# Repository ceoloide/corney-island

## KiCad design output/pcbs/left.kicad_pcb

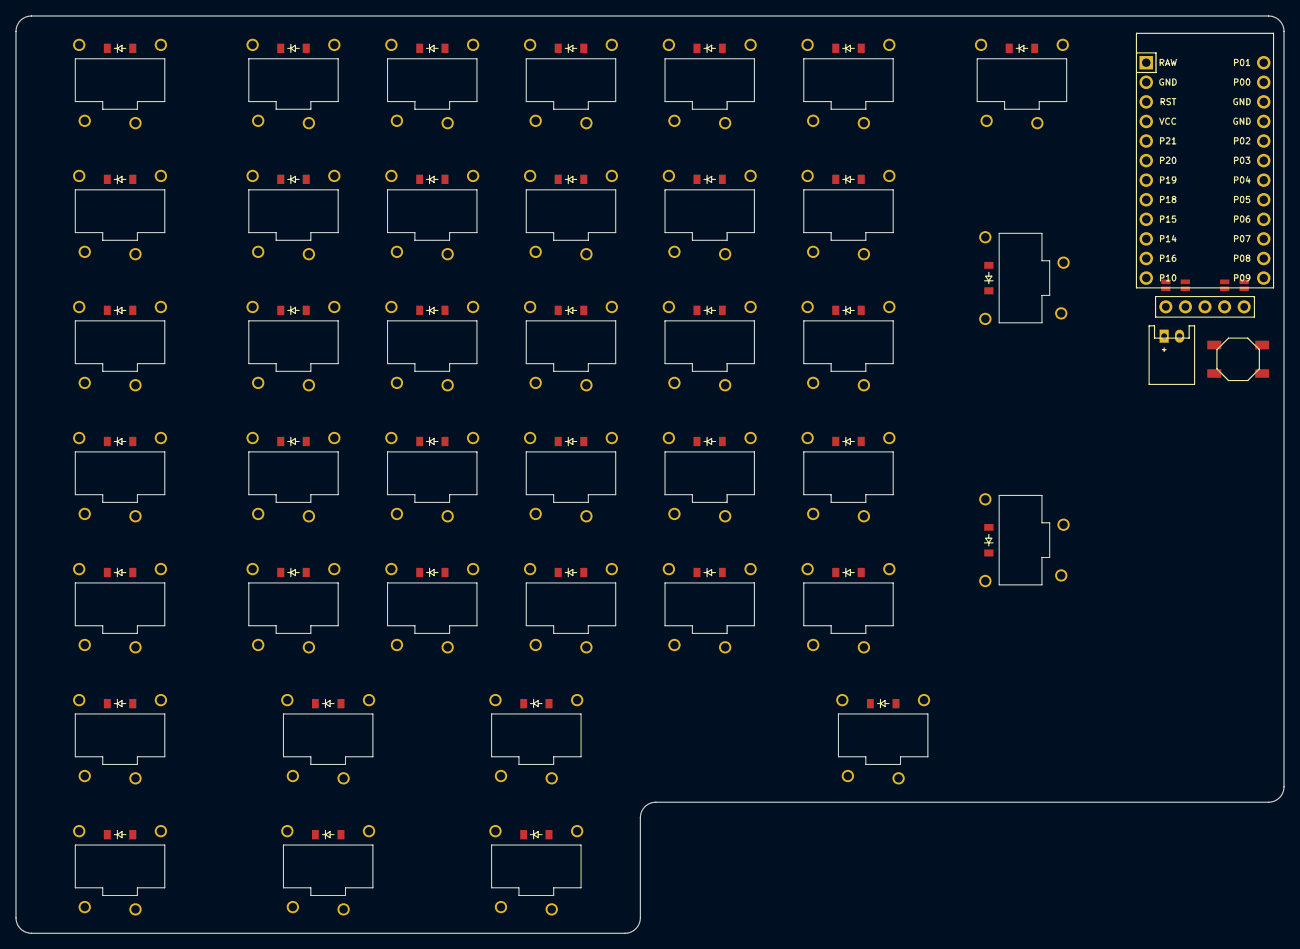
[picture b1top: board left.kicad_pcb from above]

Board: 2 copper layers, 164.5 x 119.0 mm, 164 parts (0 on the bottom side), 106 nets, no tracks yet.

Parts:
B1: SW_TACT_ALPS_SKQGABE010
D1, D2, D3, D4, D5, D6, D7, D8, D9, D10, D11, D12, D13, D14, D15, D16, D17, D18, D19, D20, D21, D22, D23, D24, D25, D26, D27, D28, D29, D30, D31, D32, D33, D34, D35, D36, D37, D38, D39, D40, D41, D42, D43, D44, D45, D46, D47, D48, D49, D50, D51, D52, D53, D54, D55, D56, D57, D58, D59, D60, D61, D62, D63, D64, D65, D66, D67, D68, D69, D70, D71, D72, D73, D74, D75, D76, D77, D78, D79, D80, D81, D82, D83, D84, D85, D86, D87, D88, D89, D90, D91, D92, D93, D94, D95, D96, D97, D98, D99, D100, D101, D102, D103, D104, D105, D106, D107, D108, D109, D110, D111, D112, D113, D114, D115, D116, D117, D118, D119, D120: ComboDiode
DISP1: nice!view
JST1: JST_PH_S2B-PH-K_02x2.00mm_Angled
MCU1: ProMicro
S1, S2, S3, S4, S5, S6, S7, S8, S9, S10, S11, S12, S13, S14, S15, S16, S17, S18, S19, S20, S21, S22, S23, S24, S25, S26, S27, S28, S29, S30, S31, S32, S33, S34, S35, S36, S37, S38, S39, S40: Kailh_PG1232

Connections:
BAT_P: JST1.1, MCU1.1
C0: MCU1.5, S1.2, S2.2, S3.2, S4.2, S5.2, S31.2, S32.2
C1: MCU1.6, S6.2, S7.2, S8.2, S9.2, S10.2, S33.2, S34.2
C2: MCU1.7, S11.2, S12.2, S13.2, S14.2, S15.2, S35.2, S36.2
C3: MCU1.8, S16.2, S17.2, S18.2, S19.2, S20.2
C4: MCU1.9, S21.2, S22.2, S23.2, S24.2, S25.2, S38.2
C5: MCU1.10, S26.2, S27.2, S28.2, S29.2, S30.2
C6: MCU1.11, S37.2, S39.2, S40.2
DISP1_1: DISP1.1, DISP1.10, DISP1.23
DISP1_2: DISP1.2, DISP1.11, DISP1.22
DISP1_4: DISP1.4, DISP1.12, DISP1.21
DISP1_5: DISP1.5, DISP1.13, DISP1.20
DPC: DISP1.15, DISP1.25, MCU1.13
DPD: DISP1.14, DISP1.24, MCU1.14
DPE: DISP1.17, DISP1.27, MCU1.17
GND: B1.1, D41.1, D42.1, D43.1, D44.1, D45.1, D46.1, D47.1, D48.1, D49.1, D50.1, D51.1, D52.1, D53.1, D54.1, D55.1, D56.1, D57.1, D58.1, D59.1, D60.1, D61.1, D62.1, D63.1, D64.1, D65.1, D66.1, D67.1, D68.1, D69.1, D70.1, D71.1, D72.1, D73.1, D74.1, D75.1, D76.1, D77.1, D78.1, D79.1, D80.1, D119.1, D120.1, DISP1.16, DISP1.26, JST1.2, MCU1.2, MCU1.15, MCU1.16
R0: D5.1, D10.1, D15.1, D20.1, D25.1, D30.1, D37.1
R1: D4.1, D9.1, D14.1, D19.1, D24.1, D29.1, D40.1, MCU1.18
R2: D3.1, D8.1, D13.1, D18.1, D23.1, D28.1, D39.1, MCU1.19
R3: D2.1, D7.1, D12.1, D17.1, D22.1, D27.1, MCU1.20
R4: D1.1, D6.1, D11.1, D16.1, D21.1, D26.1, MCU1.21
R6: D32.1, D34.1, D36.1, D38.1, MCU1.23
R7: D31.1, D33.1, D35.1, MCU1.24
RST: B1.2, MCU1.3
VCC: DISP1.3, MCU1.4
bl_e_bottomR4: D56.2, D96.2
bl_e_fR0: D60.2, D100.2
bl_e_homeR3: D57.2, D97.2
bl_e_numR1: D59.2, D99.2
bl_e_topR2: D58.2, D98.2
bl_left_bottomR4: D41.2, D81.2
bl_left_fR0: D45.2, D85.2
bl_left_homeR3: D42.2, D82.2
bl_left_numR1: D44.2, D84.2
bl_left_topR2: D43.2, D83.2
bl_one_backR1: D80.2, D120.2
bl_one_downR7: D71.2, D111.2
bl_one_enterR2: D79.2, D119.2
bl_one_fR0: D77.2, D117.2
bl_one_upR6: D72.2, D112.2
bl_pwr: D81.1, D82.1, D83.1, D84.1, D85.1, D86.1, D87.1, D88.1, D89.1, D90.1, D91.1, D92.1, D93.1, D94.1, D95.1, D96.1, D97.1, D98.1, D99.1, D100.1, D101.1, D102.1, D103.1, D104.1, D105.1, D106.1, D107.1, D108.1, D109.1, D110.1, D111.1, D112.1, D113.1, D114.1, D115.1, D116.1, D117.1, D118.1
bl_q_bottomR4: D46.2, D86.2
bl_q_fR0: D50.2, D90.2
bl_q_homeR3: D47.2, D87.2
bl_q_numR1: D49.2, D89.2
bl_q_topR2: D48.2, D88.2
bl_r_bottomR4: D61.2, D101.2
bl_r_fR0: D65.2, D105.2
bl_r_homeR3: D62.2, D102.2
bl_r_numR1: D64.2, D104.2
bl_r_topR2: D63.2, D103.2
bl_space_spaceR6: D78.2, D118.2
bl_t_bottomR4: D66.2, D106.2
bl_t_fR0: D70.2, D110.2
bl_t_homeR3: D67.2, D107.2
bl_t_numR1: D69.2, D109.2
bl_t_topR2: D68.2, D108.2
bl_three_downR7: D75.2, D115.2
bl_three_upR6: D76.2, D116.2
bl_two_downR7: D73.2, D113.2
bl_two_upR6: D74.2, D114.2
bl_w_bottomR4: D51.2, D91.2
bl_w_fR0: D55.2, D95.2
bl_w_homeR3: D52.2, D92.2
bl_w_numR1: D54.2, D94.2
bl_w_topR2: D53.2, D93.2
e_bottom: D16.2, S16.1
e_f: D20.2, S20.1
e_home: D17.2, S17.1
e_num: D19.2, S19.1
e_top: D18.2, S18.1
left_bottom: D1.2, S1.1
left_f: D5.2, S5.1
left_home: D2.2, S2.1
left_num: D4.2, S4.1
left_top: D3.2, S3.1
one_back: D40.2, S40.1
one_down: D31.2, S31.1
one_enter: D39.2, S39.1
one_f: D37.2, S37.1
one_up: D32.2, S32.1
q_bottom: D6.2, S6.1
q_f: D10.2, S10.1
q_home: D7.2, S7.1
q_num: D9.2, S9.1
q_top: D8.2, S8.1
r_bottom: D21.2, S21.1
r_f: D25.2, S25.1
r_home: D22.2, S22.1
r_num: D24.2, S24.1
r_top: D23.2, S23.1
space_space: D38.2, S38.1
t_bottom: D26.2, S26.1
t_f: D30.2, S30.1
t_home: D27.2, S27.1
t_num: D29.2, S29.1
t_top: D28.2, S28.1
three_down: D35.2, S35.1
three_up: D36.2, S36.1
two_down: D33.2, S33.1
two_up: D34.2, S34.1
w_bottom: D11.2, S11.1
w_f: D15.2, S15.1
w_home: D12.2, S12.1
w_num: D14.2, S14.1
w_top: D13.2, S13.1
